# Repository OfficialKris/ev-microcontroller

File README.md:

# EV Microcontroller

## Description

The EV Microcontroller is a small, portable, self-contained
processing unit that is capable of reading in sensor data
and outputing that data to a CAN bus. It is meant to be a
robust alternative to a similar unit made of an arduino and 
compatable shields.

## Features

* Low power, shock resistant
* CAN connectivity
* 5 12-bit analog pins
* 10 digital pins
* Micropython support
* RP2040 microprocessor
* Onboard power distribution (3V3, 5V, 12V)
* USB-C port (flash/debug/power/data)
* MicroSD CAN backup
* M2 grounded mounting holes (with vibration dampining)
* Board thermistor
* 9 axis gyroscope
* Highly embedded and compact (30mm x 40mm)
* Electrical protections (overcurrent, undervoltage, etc.)
* Waterproof enclosure
* Other features when paired with other devices (display, etc.)

## Parts

| Type | Part | Description |
|------|------|-------------|
| MCU |RP2040| Microcontroller |
| Power |TCKE805NL,RF| eFuse |
| Power |MAX77540AAWV+| Dual Voltage Regulator |
| Power |FPF3042UCX| Power Source Switch |
| Memory |GD25Q40CEIGR| Flash |
| Memory |MEM2051-00-195-00-A| MicroSD connector |
| Peripherals |TJA1441BTK/0Z| CAN Transceiver |
| Peripherals |MAX19777AZA+T| ADC |
| Peripherals |MC6470| 9-axis IMU |
| Peripherals |NTCG104QH474JT1| Board thermistor |
| Connectors |USB4105-GF-A| USB C Receptacle |
| Connectors |B20B-PHDSS(LF)(SN)| 20 pin JST Connector |
| Oscillator |DSC1001DI1-020.0000| 20Mhz oscillator |

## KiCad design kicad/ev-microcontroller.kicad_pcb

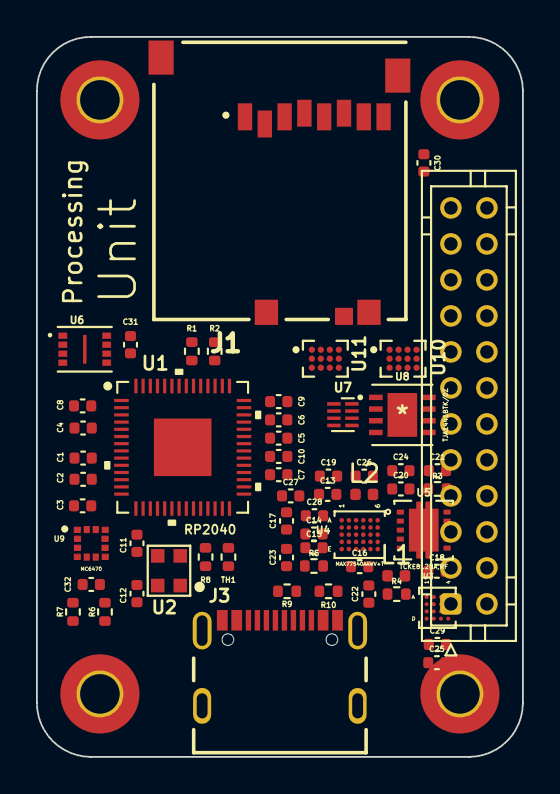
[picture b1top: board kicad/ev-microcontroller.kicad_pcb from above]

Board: 2 copper layers, 27.0 x 40.0 mm, 63 parts (0 on the bottom side), 57 nets, no tracks yet.

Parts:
C1, C2, C3, C4, C5, C6, C7, C8, C9, C10, C12, C13, C14, C20, C23, C24, C25, C27, C30, C31, C32: 0.1µF; C_0402_1005Metric
C11: 15pF; C_0402_1005Metric
C15, C16, C17, C22, C26, C28, C29: 22µF; C_0402_1005Metric
C18, C19: 1µF; C_0402_1005Metric
C21: 100pF; C_0402_1005Metric
H1, H2, H3, H4: M2; MountingHole_2.2mm_M2_Pad_TopBottom
J1: MEM2051-00-195-00-A_REVC; GCT_MEM2051-00-195-00-A_REVC
J2: Conn_02x20_Odd_Even; JST_PHD_B24B-PHDSS_2x12_P2.00mm_Vertical
J3: USB4105-GF-A; GCT_USB4105-GF-A
L1, L2: 0.47µH; L_0402_1005Metric
R1, R2: 27.4; R_0402_1005Metric
R3: 36k; R_0402_1005Metric
R4: 75k; R_0402_1005Metric
R5: 100k; R_0402_1005Metric
R6, R7: 4.7k; R_0402_1005Metric
R8: 470k; R_0402_1005Metric
R9, R10: 5.1k; R_0402_1005Metric
TH1: NTC; R_0402_1005Metric
U1: RP2040; IC57_RP2040
U2: DSC1001DI1-025.0000T; OSCDFN250X200X89-4N
U3: FPF3042UCX
U4: MAX77540AAWV+T; 21-100414_W302P2Z+1_MXM
U5: TCKE812NA,RF; WSON10B_TOS
U6: GD25Q40CEIGR; PSON50P200X300X50-9N
U7: UM3202; DFN-8_1.7x1.35mm_P0.4mm
U8: TJA1441BTK/0Z; HVSON8_TJA1441BTK_0Z_NXP
U9: MC6470; PQFN50P200X200X100-12N
U10, U11: MAX11613EWCT; BGA12N50P3X4_188X221X69N

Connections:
+1V1: C8.1, C9.1, C10.1, U1.23 (DVDD), U1.45 (VREG_VOUT), U1.50 (DVDD)
+3V3: C1.1, C2.1, C3.1, C4.1, C5.1, C6.1, C7.1, C12.1, C22.2, C26.2, C29.2, C30.1, C31.1, C32.1, J1.4 (VDD), J2.11, J2.13, L2.1, R6.1, R7.1, R8.1, U1.1 (IOVDD), U1.10 (IOVDD), U1.22 (IOVDD), U1.26 (RUN), U1.33 (IOVDD), U1.42 (IOVDD), U1.43 (ADC_AVDD), U1.44 (VREG_VIN), U1.48 (USB_VDD), U1.49 (IOVDD), U2.4 (VDD), U4.C6 (SNS2), U6.8 (VCC), U10.C1 (VDD), U11.C1 (VDD)
+5V: C15.2, C16.2, C17.2, J2.12, J2.14, L1.1, U4.C1 (SNS1), U8.3 (VCC)
/MCU/CLOCK: C11.1, U1.20 (XIN), U2.3 (OUT)
/Power/V_OUT: C19.1, C27.1, C28.2, U4.A3 (IN1), U4.A4 (IN2), U4.C2 (EN1), U4.C5 (EN2), U4.E5 (SYS), U5.6 (VOUT), U5.7 (VOUT), U5.8 (VOUT)
CAN_HI: J2.2, J2.4
CAN_LO: J2.1, J2.3, U8.6 (CANL)
DN: J3.A7 (DN1), J3.B7 (DN2), R2.2
DP: J3.A6 (DP1), J3.B6 (DP2), R1.2
GND: C1.2, C2.2, C3.2, C4.2, C5.2, C6.2, C7.2, C8.2, C9.2, C10.2, C11.2, C12.2, C13.2, C14.1, C15.1, C16.1, C17.1, C18.2, C19.2, C21.2, C22.1, C23.2, C24.2, C26.1, C27.2, C28.1, C29.1, C30.2, C31.2, H1.1, H2.1, H3.1, H4.1, J1.6 (VSS), J1.10 (SHIELD), J1.11 (SHIELD), J1.12 (SHIELD), J1.13 (SHIELD), J2.8, J2.15, J2.16, J3.A1_B12 (GND), J3.B1_A12 (GND), J3.S1 (SHELL_GND), J3.S2 (SHELL_GND), J3.S3 (SHELL_GND), J3.S4 (SHELL_GND), R3.2, R4.2, R5.1, R9.2, R10.1, TH1.2, U1.19 (TESTEN), U1.57 (GND), U2.2 (GND), U3.D1 (GND), U3.D2 (GND), U4.A1 (PGND1), U4.A6 (PGND2), U4.C3 (I2C_EN), U4.C4 (IRQB), U4.D3 (ADDR), U4.D5 (ALT_IN), U4.D6 (SDA), U4.E3 (AGND), U4.E6 (SCL), U5.11 (GND), U6.4 (VSS), U8.2 (GND), U8.8 (S), U9.1 (A5), U9.9 (GND), U10.B1 (GND), U10.B2 (GND), U10.B3 (GND), U10.B4 (GND), U10.C2 (GND), U11.B1 (GND), U11.B2 (GND), U11.B3 (GND), U11.B4 (GND), U11.C2 (GND)
GPIO_1: J2.18, U1.29 (GPIO18)
GPIO_2: J2.20, U1.30 (GPIO19)
GPIO_3: J2.22, U1.31 (GPIO20)
GPIO_4: J2.24, U1.32 (GPIO21)
GPIO_8: U1.18 (GPIO15), U1.37 (GPIO25)
GPIO_12_A1: J2.17, U1.41 (GPIO29/ADC3)
GPIO_13_A2: J2.19, U1.40 (GPIO28/ADC2)
GPIO_14_A3: J2.21, U1.39 (GPIO27/ADC1)
GPIO_CAN_TXD: U1.27 (GPIO16), U1.28 (GPIO17)
GPIO_CD: J1.9 (CD), U1.13 (GPIO10)
GPIO_TEMP: R8.2, TH1.1, U1.38 (GPIO26/ADC0)
unnamed: C18.1, U4.E1 (FPWM1B), U4.E2 (FPWM2B), U4.E4 (VL)
unnamed: C20.1, U4.B1 (BST1)
unnamed: C20.2, L1.2, U4.A2 (LX1), U4.B2 (LX1)
unnamed: C21.1, U5.1 (DV/DT)
unnamed: C23.1, U4.D4 (VDD)
unnamed: C25.1, U4.B6 (BST2)
unnamed: C25.2, L2.2, U4.A5 (LX2), U4.B5 (LX2)
unnamed: C32.2, U9.3 (VDDIO), U9.7 (VDDM)
unnamed: J3.A5 (CC1), R9.1
unnamed: J3.B5 (CC2), R10.2
unnamed: R1.1, U1.47 (USB_DP)
unnamed: R2.1, U1.46 (USB_DM)
unnamed: R3.1, U5.10 (ILIM)
unnamed: R4.1, U4.D2 (SEL2)
unnamed: R5.2, U4.D1 (SEL1)
QSPI_SCLK: U1.52 (QSPI_SCLK), U6.6 (SCLK)
QSPI_SD0: U1.53 (QSPI_SD0), U6.5 (SI(IO0))
QSPI_SD1: U1.55 (QSPI_SD1), U6.2 (SO(IO1))
QSPI_SD2: U1.54 (QSPI_SD2), U6.3 (WP#(IO2))
QSPI_SD3: U1.51 (QSPI_SD3), U6.7 (HOLD#(IO3))
QSPI_SS: U1.56 (QSPI_SS_N), U6.1 (CS#)
SCL_0: U1.12 (GPIO9), U11.C4 (SCL)
SCL_1: R7.2, U1.9 (GPIO7), U9.12 (SCL), U10.C4 (SCL)
SDA_0: U1.11 (GPIO8), U11.C3 (SDA)
SDA_1: R6.2, U1.8 (GPIO6), U9.2 (SDA), U10.C3 (SDA)
SD_CLK: J1.5 (CLK), U1.7 (GPIO5)
SD_CMD: J1.3 (CMD), U1.6 (GPIO4)
SD_DAT0: J1.7 (DAT0), U1.2 (GPIO0)
SD_DAT1: J1.8 (DAT1), U1.3 (GPIO1)
SD_DAT2: J1.1 (DAT2), U1.4 (GPIO2)
SD_DAT3: J1.2 (CD/DAT3), U1.5 (GPIO3)
SWCIK: J2.9, U1.24 (SWCLK)
SWDIO: J2.10, U1.25 (SWDIO)
VIN: U3.A4 (VIN), U3.B4 (VIN), U3.C4 (VIN)
V_BUS: C14.2, J3.A4_B9 (VBUS), J3.B4_A9 (VBUS), U3.A1 (VBUS), U3.B1 (VBUS), U3.C1 (VBUS)
V_SEL: C13.1, C24.1, U3.A2 (VOUT), U3.A3 (VOUT), U3.B3 (VOUT), U3.C3 (VOUT), U5.2 (EN/UVLO), U5.3 (VIN), U5.4 (VIN), U5.5 (VIN)

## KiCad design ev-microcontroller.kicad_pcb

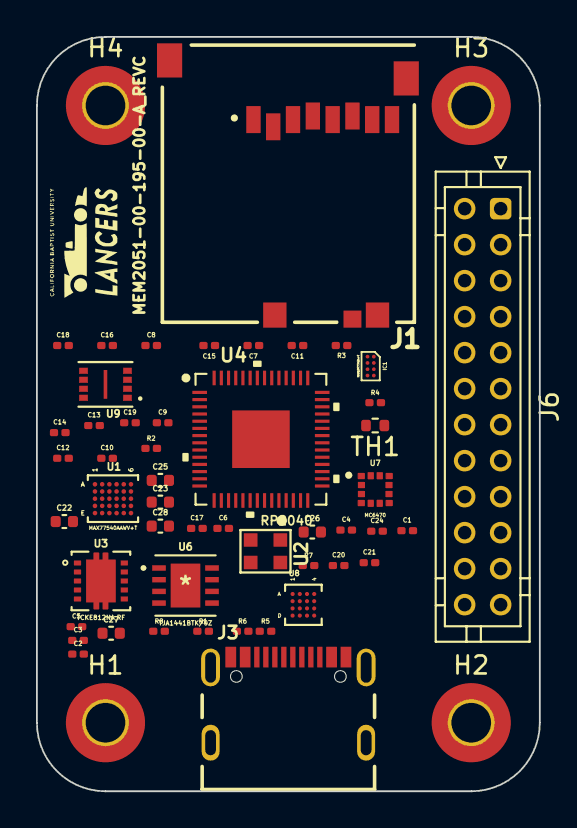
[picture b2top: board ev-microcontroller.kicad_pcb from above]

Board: 2 copper layers, 27.9 x 41.9 mm, 53 parts (0 on the bottom side), 35 nets, no tracks yet.

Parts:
C1, C2, C4, C5, C6, C7, C8, C9, C10, C11, C12, C13, C14, C15, C16, C17, C19, C24: 0.1µF; C_0201_0603Metric
C3: 100pF; C_0201_0603Metric
C18: 15pF; C_0201_0603Metric
C20, C21: 1µF; C_0201_0603Metric
C22, C23, C25, C26, C27, C28: 22µF; C_0402_1005Metric
H1, H2, H3, H4: M2; MountingHole_2.2mm_M2_Pad_TopBottom
IC1: MAX19777AZA+T; BGA8C35P4X2_143X86X37
J1: MEM2051-00-195-00-A_REVC; GCT_MEM2051-00-195-00-A_REVC
J3: USB4105-GF-A; GCT_USB4105-GF-A
J6: Conn_02x12_Counter_Clockwise; JST_PHD_B24B-PHDSS_2x12_P2.00mm_Vertical
R1: 36k; R_0201_0603Metric
R2, R3: 27.4; R_0201_0603Metric
R4: 470k; R_0201_0603Metric
R5, R6: 5.1k; R_0201_0603Metric
R7: 75k; R_0201_0603Metric
R8: 100k; R_0201_0603Metric
TH1: NTC; R_0402_1005Metric
U1: MAX77540AAWV+T; 21-100414_W302P2Z+1_MXM
U2: DSC1001DI1-025.0000T; OSCDFN250X200X89-4N
U3: TCKE812NA,RF; WSON10B_TOS
U4: RP2040; IC57_RP2040
U6: TJA1441BTK/0Z; HVSON8_TJA1441BTK_0Z_NXP
U7: MC6470; PQFN50P200X200X100-12N
U8: WLCSP16_1P96X1P76X0P586_567SE_ONS; FPF3042UCX
U9: GD25Q40CEIGR; PSON50P200X300X50-9N

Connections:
+1V1: C14.1, C15.1, C16.1, U4.23 (DVDD), U4.45 (VREG_VOUT), U4.50 (DVDD)
+5V: C22.2, C25.2, C27.2
/MCU/CLOCK: C18.1, U2.3 (OUT), U4.20 (XIN)
/Power/V_OUT: C5.1, C21.1, U1.A3 (IN1), U1.A4 (IN2), U1.C2 (EN1), U1.C5 (EN2), U1.E5 (SYS), U3.6 (VOUT), U3.7 (VOUT), U3.8 (VOUT)
CAN_HI: J6.11, J6.12
CAN_LO: J6.13, J6.14
DN: J3.A7 (DN1), J3.B7 (DN2), R3.2
DP: J3.A6 (DP1), J3.B6 (DP2), R2.2
GND: C1.2, C2.1, C3.2, C4.2, C5.2, C6.2, C7.2, C8.2, C9.2, C10.2, C11.2, C12.2, C13.2, C14.2, C15.2, C16.2, C17.2, C18.2, C19.2, C20.2, C21.2, C22.1, C23.1, C24.2, C25.1, C26.1, C27.1, C28.1, H1.1, H2.1, H3.1, H4.1, J1.6 (VSS), J1.10 (SHIELD), J1.11 (SHIELD), J1.12 (SHIELD), J1.13 (SHIELD), J3.A1_B12 (GND), J3.B1_A12 (GND), J3.S1 (SHELL_GND), J3.S2 (SHELL_GND), J3.S3 (SHELL_GND), J3.S4 (SHELL_GND), R1.2, R5.2, R6.1, R7.2, R8.1, TH1.2, U1.A1 (PGND1), U1.A6 (PGND2), U1.C3 (I2C_EN), U1.C4 (IRQB), U1.D3 (ADDR), U1.D6 (SDA), U1.E3 (AGND), U1.E6 (SCL), U2.2 (GND), U3.11 (GND), U4.19 (TESTEN), U4.57 (GND), U8.D1 (GND), U8.D2 (GND), U9.4 (VSS)
GPIO_TEMP: R4.2, TH1.1, U4.38 (GPIO26/ADC0)
IO_FILTERING: C6.1, C7.1, C8.1, C9.1, C10.1, C11.1, C12.1, C13.1, C17.1, C19.1, C23.2, C26.2, C28.2, J1.4 (VDD), R4.1, U2.4 (VDD), U4.1 (IOVDD), U4.10 (IOVDD), U4.22 (IOVDD), U4.33 (IOVDD), U4.42 (IOVDD), U4.43 (ADC_AVDD), U4.44 (VREG_VIN), U4.48 (USB_VDD), U4.49 (IOVDD), U9.8 (VCC)
unnamed: C3.1, U3.1 (DV/DT)
unnamed: J3.A5 (CC1), R5.1
unnamed: J3.B5 (CC2), R6.2
unnamed: R2.1, U4.47 (USB_DP)
unnamed: R3.1, U4.46 (USB_DM)
unnamed: R8.2, U1.D1 (SEL1)
unnamed: R7.1, U1.D2 (SEL2)
unnamed: C24.1, U1.D4 (VDD)
unnamed: C20.1, U1.E1 (FPWM1B), U1.E2 (FPWM2B), U1.E4 (VL)
unnamed: R1.1, U3.10 (ILIM)
QSPI_SCLK: U4.52 (QSPI_SCLK), U9.6 (SCLK)
QSPI_SD0: U4.53 (QSPI_SD0), U9.5 (SI(IO0))
QSPI_SD1: U4.55 (QSPI_SD1), U9.2 (SO(IO1))
QSPI_SD2: U4.54 (QSPI_SD2), U9.3 (WP#(IO2))
QSPI_SD3: U4.51 (QSPI_SD3), U9.7 (HOLD#(IO3))
SD_CLK: J1.5 (CLK), U4.7 (GPIO5)
SD_CMD: J1.3 (CMD), U4.6 (GPIO4)
SD_DAT0: J1.7 (DAT0), U4.2 (GPIO0)
SD_DAT1: J1.8 (DAT1), U4.3 (GPIO1)
SD_DAT2: J1.1 (DAT2), U4.4 (GPIO2)
SD_DAT3: J1.2 (CD/DAT3), U4.5 (GPIO3)
VIN: U8.A4 (VIN), U8.B4 (VIN), U8.C4 (VIN)
V_BUS: C2.2, J3.A4_B9 (VBUS), J3.B4_A9 (VBUS), U8.A1 (VBUS), U8.B1 (VBUS), U8.C1 (VBUS)
V_SEL: C1.1, C4.1, U3.2 (EN/UVLO), U3.3 (VIN), U3.4 (VIN), U3.5 (VIN), U8.A2 (VOUT), U8.A3 (VOUT), U8.B3 (VOUT), U8.C3 (VOUT)

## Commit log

2022-05-13 Initial KiCad 6.0 commit
2022-05-13 Added initial README
2022-05-14 Added gitignore
2022-05-14 Added external components and updated schematic info
2022-05-14 Added NCP1090DRG symbol library
2022-05-14 Updated sym-lib-table with NCP1090DRG.kicad_sym
2022-06-25 Updated .gitignore
2022-06-25 First major revision
2022-06-25 Moved KiCad files to separate folder
2022-06-30 Connected all remaining unconnected pins
2022-07-10 Updated symbol and footprint libraries
    Added descriptions to symbols
    Added new footprints for power supply refactor
2022-07-10 Added LICENSE
2022-10-08 Updated .gitignore to ignore backups
2022-10-08 Updated schematic with various changes
    Increased size of small components
    Updated title/spec sheet
    Cleaned footprints
    Other small changes as well
2022-10-09 Changed pinout on main pcb connector
2022-10-09 Modified size of pcb board
